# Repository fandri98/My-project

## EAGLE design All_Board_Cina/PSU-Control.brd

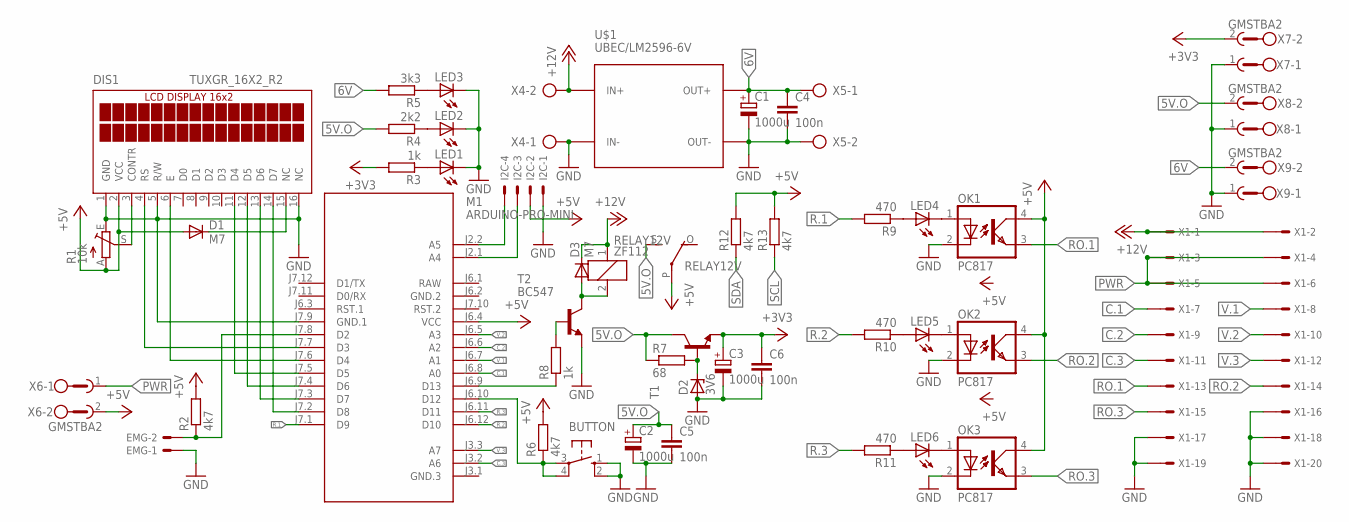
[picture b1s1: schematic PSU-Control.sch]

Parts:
BUTTON: 40-XX; B3F-40XX
C1, C2, C3: 1000u; E5-10,5
C4, C5, C6: 100n; C0805K
D1, D3: M7; DO214AA
D2: 3V6; ZDIO-7.5
DIS1: TUXGR_16X2_R2
EMG: 22-23-2021
I2C: 22-23-2041
LED1, LED2, LED3, LED4, LED5, LED6: LEDCHIPLED_1206; CHIPLED_1206
M1: ARDUINO-PRO-MINI; ARDUINO-PRO-MINI#NP
OK1, OK2, OK3: PC817; DIL04
R1: 10k; RJ9W
R2, R6, R12, R13: 4k7; R0805
R3, R8: 1k; R0805
R4: 2k2; R0805
R5: 3k3; R0805
R7: 68; R0805
R9, R10, R11: 470; R0805
RELAY12V: ZF112
T1: -NPN-TO220V; TO220V
T2: BC547; TO92
U$1: UBEC/LM2596-6V; DC-DC-STEP-DOWN-LM2596
X1: 057-020-1
X4, X5: AK300/2
X6, X7, X8, X9: GMSTBA2

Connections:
5V.O: C2.+, C5.1, R4.2, R7.1, RELAY12V.S, T1.2 (C), X8.2
6V: C1.+, C4.1, R5.2, U$1.OUT+, X5.1, X9.2
+3V3: C3.+, C6.1, R3.2, T1.3 (E), X7.2
+5V: D1.A, DIS1.2 (VCC), I2C.2, M1.J6.4 (VCC), OK1.4 (COL), OK2.4 (COL), OK3.4 (COL), R1.A, R2.2, R6.2, R12.2, R13.2, RELAY12V.P, X6.2
+12V: D3.C, RELAY12V.1, U$1.IN+, X1.1, X1.2, X4.2
C.1: M1.J6.8 (A0), X1.7
C.2: M1.J6.6 (A2), X1.9
C.3: M1.J3.2 (A6), X1.11
GND: BUTTON.1 (S), BUTTON.2 (S1), C1.-, C2.-, C3.-, C4.2, C5.2, C6.2, D2.A, DIS1.1 (GND), DIS1.5 (R/W), DIS1.16 (NC), EMG.1, I2C.1, LED1.C, LED2.C, LED3.C, M1.J7.9 (GND.1), OK1.2 (C), OK2.2 (C), OK3.2 (C), R1.E, T2.1 (E), U$1.IN-, U$1.OUT-, X1.16, X1.17, X1.18, X1.19, X1.20, X4.1, X5.2, X7.1, X8.1, X9.1
GND.2: M1.J6.2 (GND.2)
unnamed: EMG.2, M1.J7.8 (D2), R2.1
unnamed: D1.C, DIS1.15 (NC)
unnamed: DIS1.4 (RS), M1.J7.7 (D3)
unnamed: DIS1.3 (CONTR), R1.S
unnamed: DIS1.6 (E), M1.J7.6 (D4)
unnamed: DIS1.11 (D4), M1.J7.5 (D5)
unnamed: LED4.C, OK1.1 (A)
unnamed: LED5.A, R10.1
unnamed: DIS1.12 (D5), M1.J7.4 (D6)
unnamed: DIS1.13 (D6), M1.J7.3 (D7)
unnamed: DIS1.14 (D7), M1.J7.2 (D8)
unnamed: BUTTON.3, BUTTON.4 (P1), M1.J6.10 (D12), R6.1
unnamed: LED1.A, R3.1
unnamed: LED2.A, R4.1
unnamed: LED3.A, R5.1
unnamed: D2.C, R7.2, T1.1 (B)
unnamed: LED5.C, OK2.1 (A)
unnamed: D3.A, RELAY12V.2, T2.3 (C)
unnamed: M1.J6.9 (D13), R8.1
unnamed: R8.2, T2.2 (B)
unnamed: LED6.A, R11.1
unnamed: LED4.A, R9.1
unnamed: LED6.C, OK3.1 (A)
PWR: X1.3, X1.4, X1.5, X1.6, X6.1
R.1: M1.J7.1 (D9), R9.2
R.2: M1.J6.12 (D10), R10.2
R.3: M1.J6.11 (D11), R11.2
RAW: M1.J6.1 (RAW)
RO.1: OK1.3 (EMIT), X1.13
RO.2: OK2.3 (EMIT), X1.14
RO.3: OK3.3 (EMIT), X1.15
SCL: I2C.4, M1.J2.2 (A5), R13.1
SDA: I2C.3, M1.J2.1 (A4), R12.1
V.1: M1.J6.7 (A1), X1.8
V.2: M1.J6.5 (A3), X1.10
V.3: M1.J3.3 (A7), X1.12

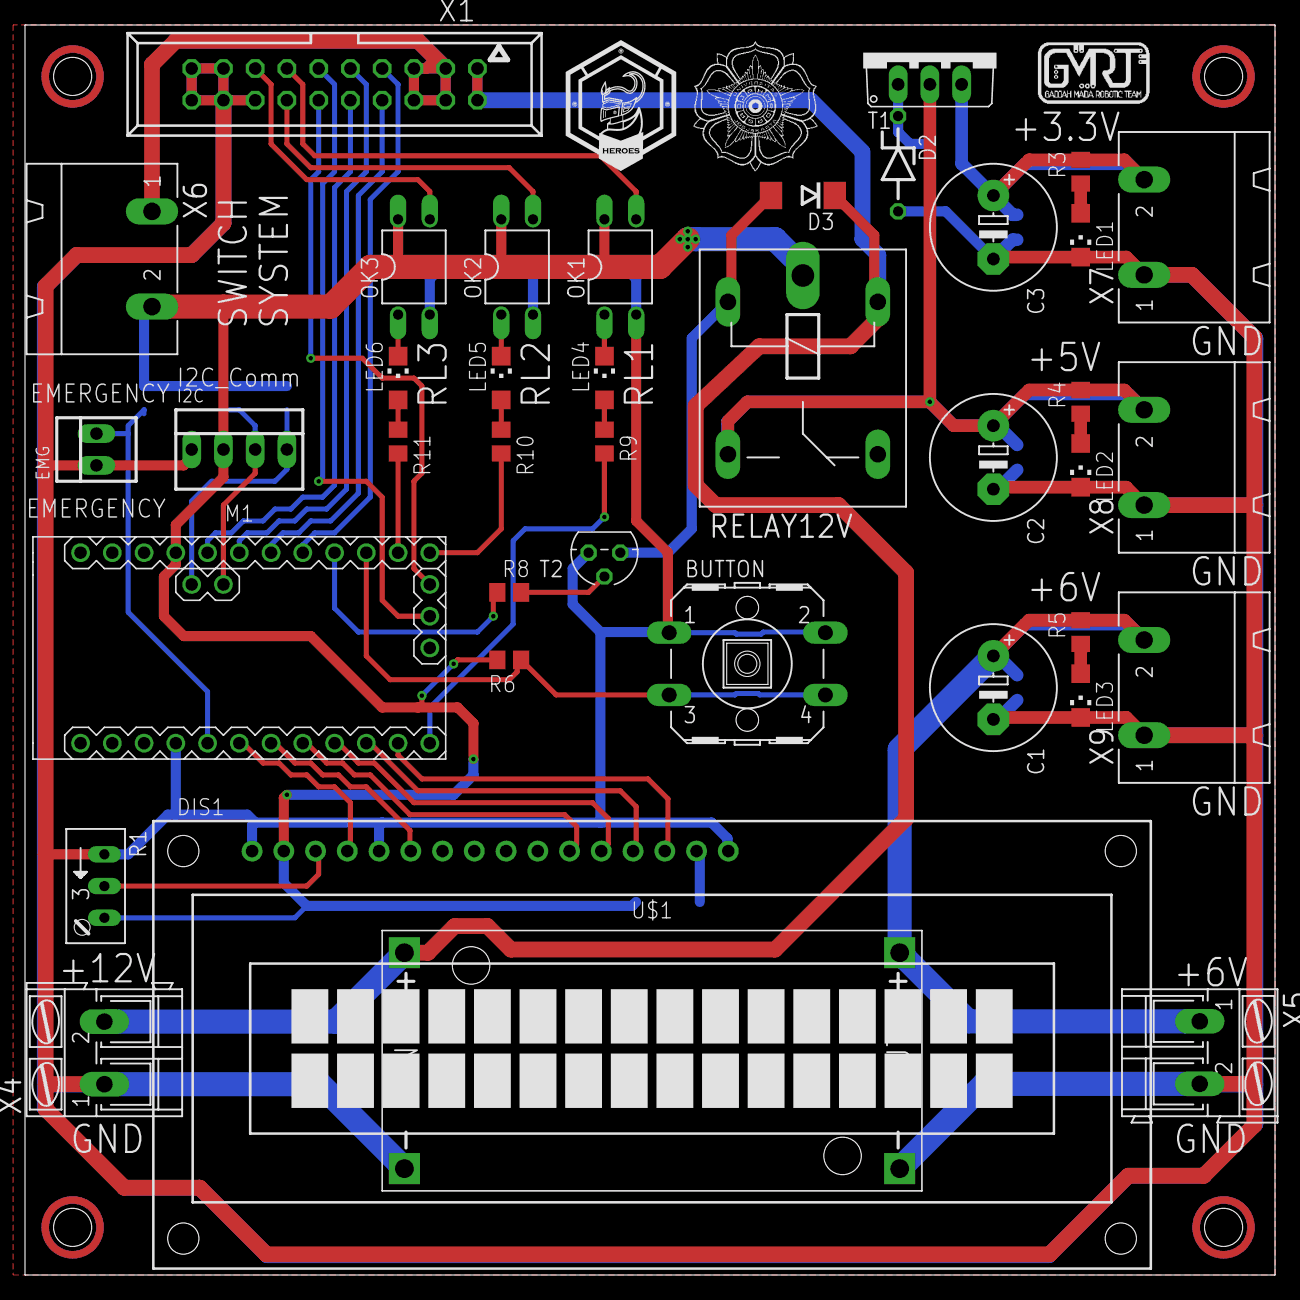
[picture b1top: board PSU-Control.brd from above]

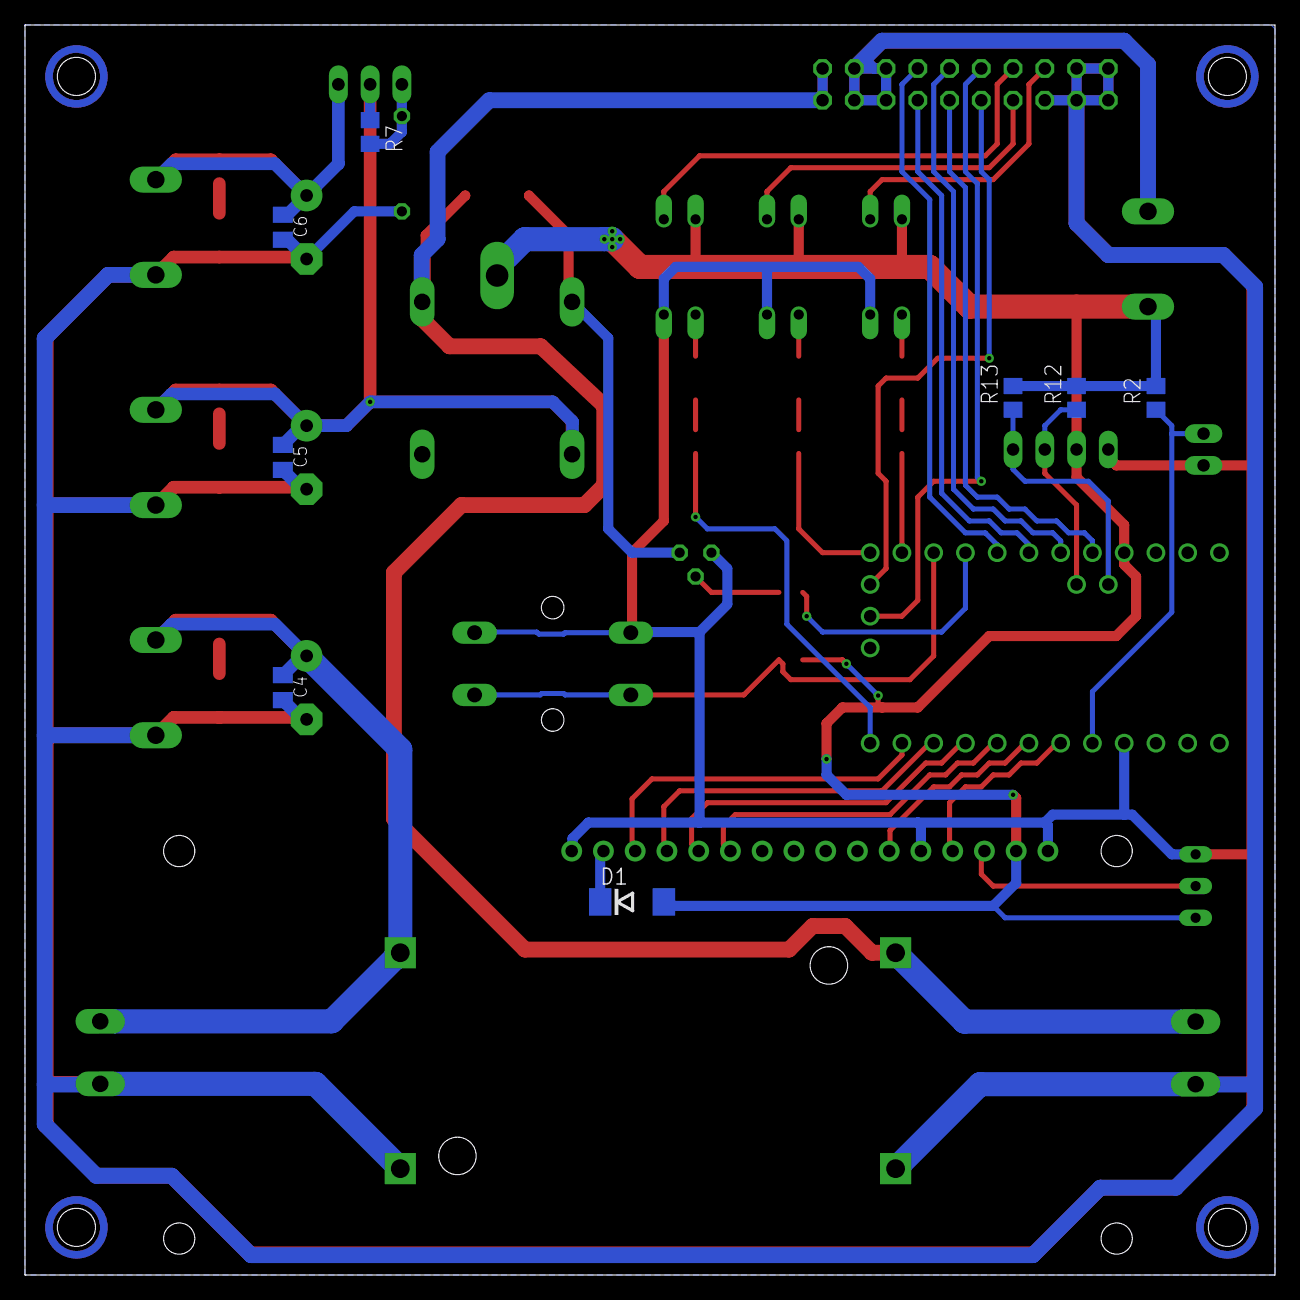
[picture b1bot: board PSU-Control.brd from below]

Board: 2 copper layers, 100.0 x 100.0 mm, 51 parts (8 on the bottom side), 44 nets.

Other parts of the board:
U$2, U$3, U$4, U$5: HOLE-3MM

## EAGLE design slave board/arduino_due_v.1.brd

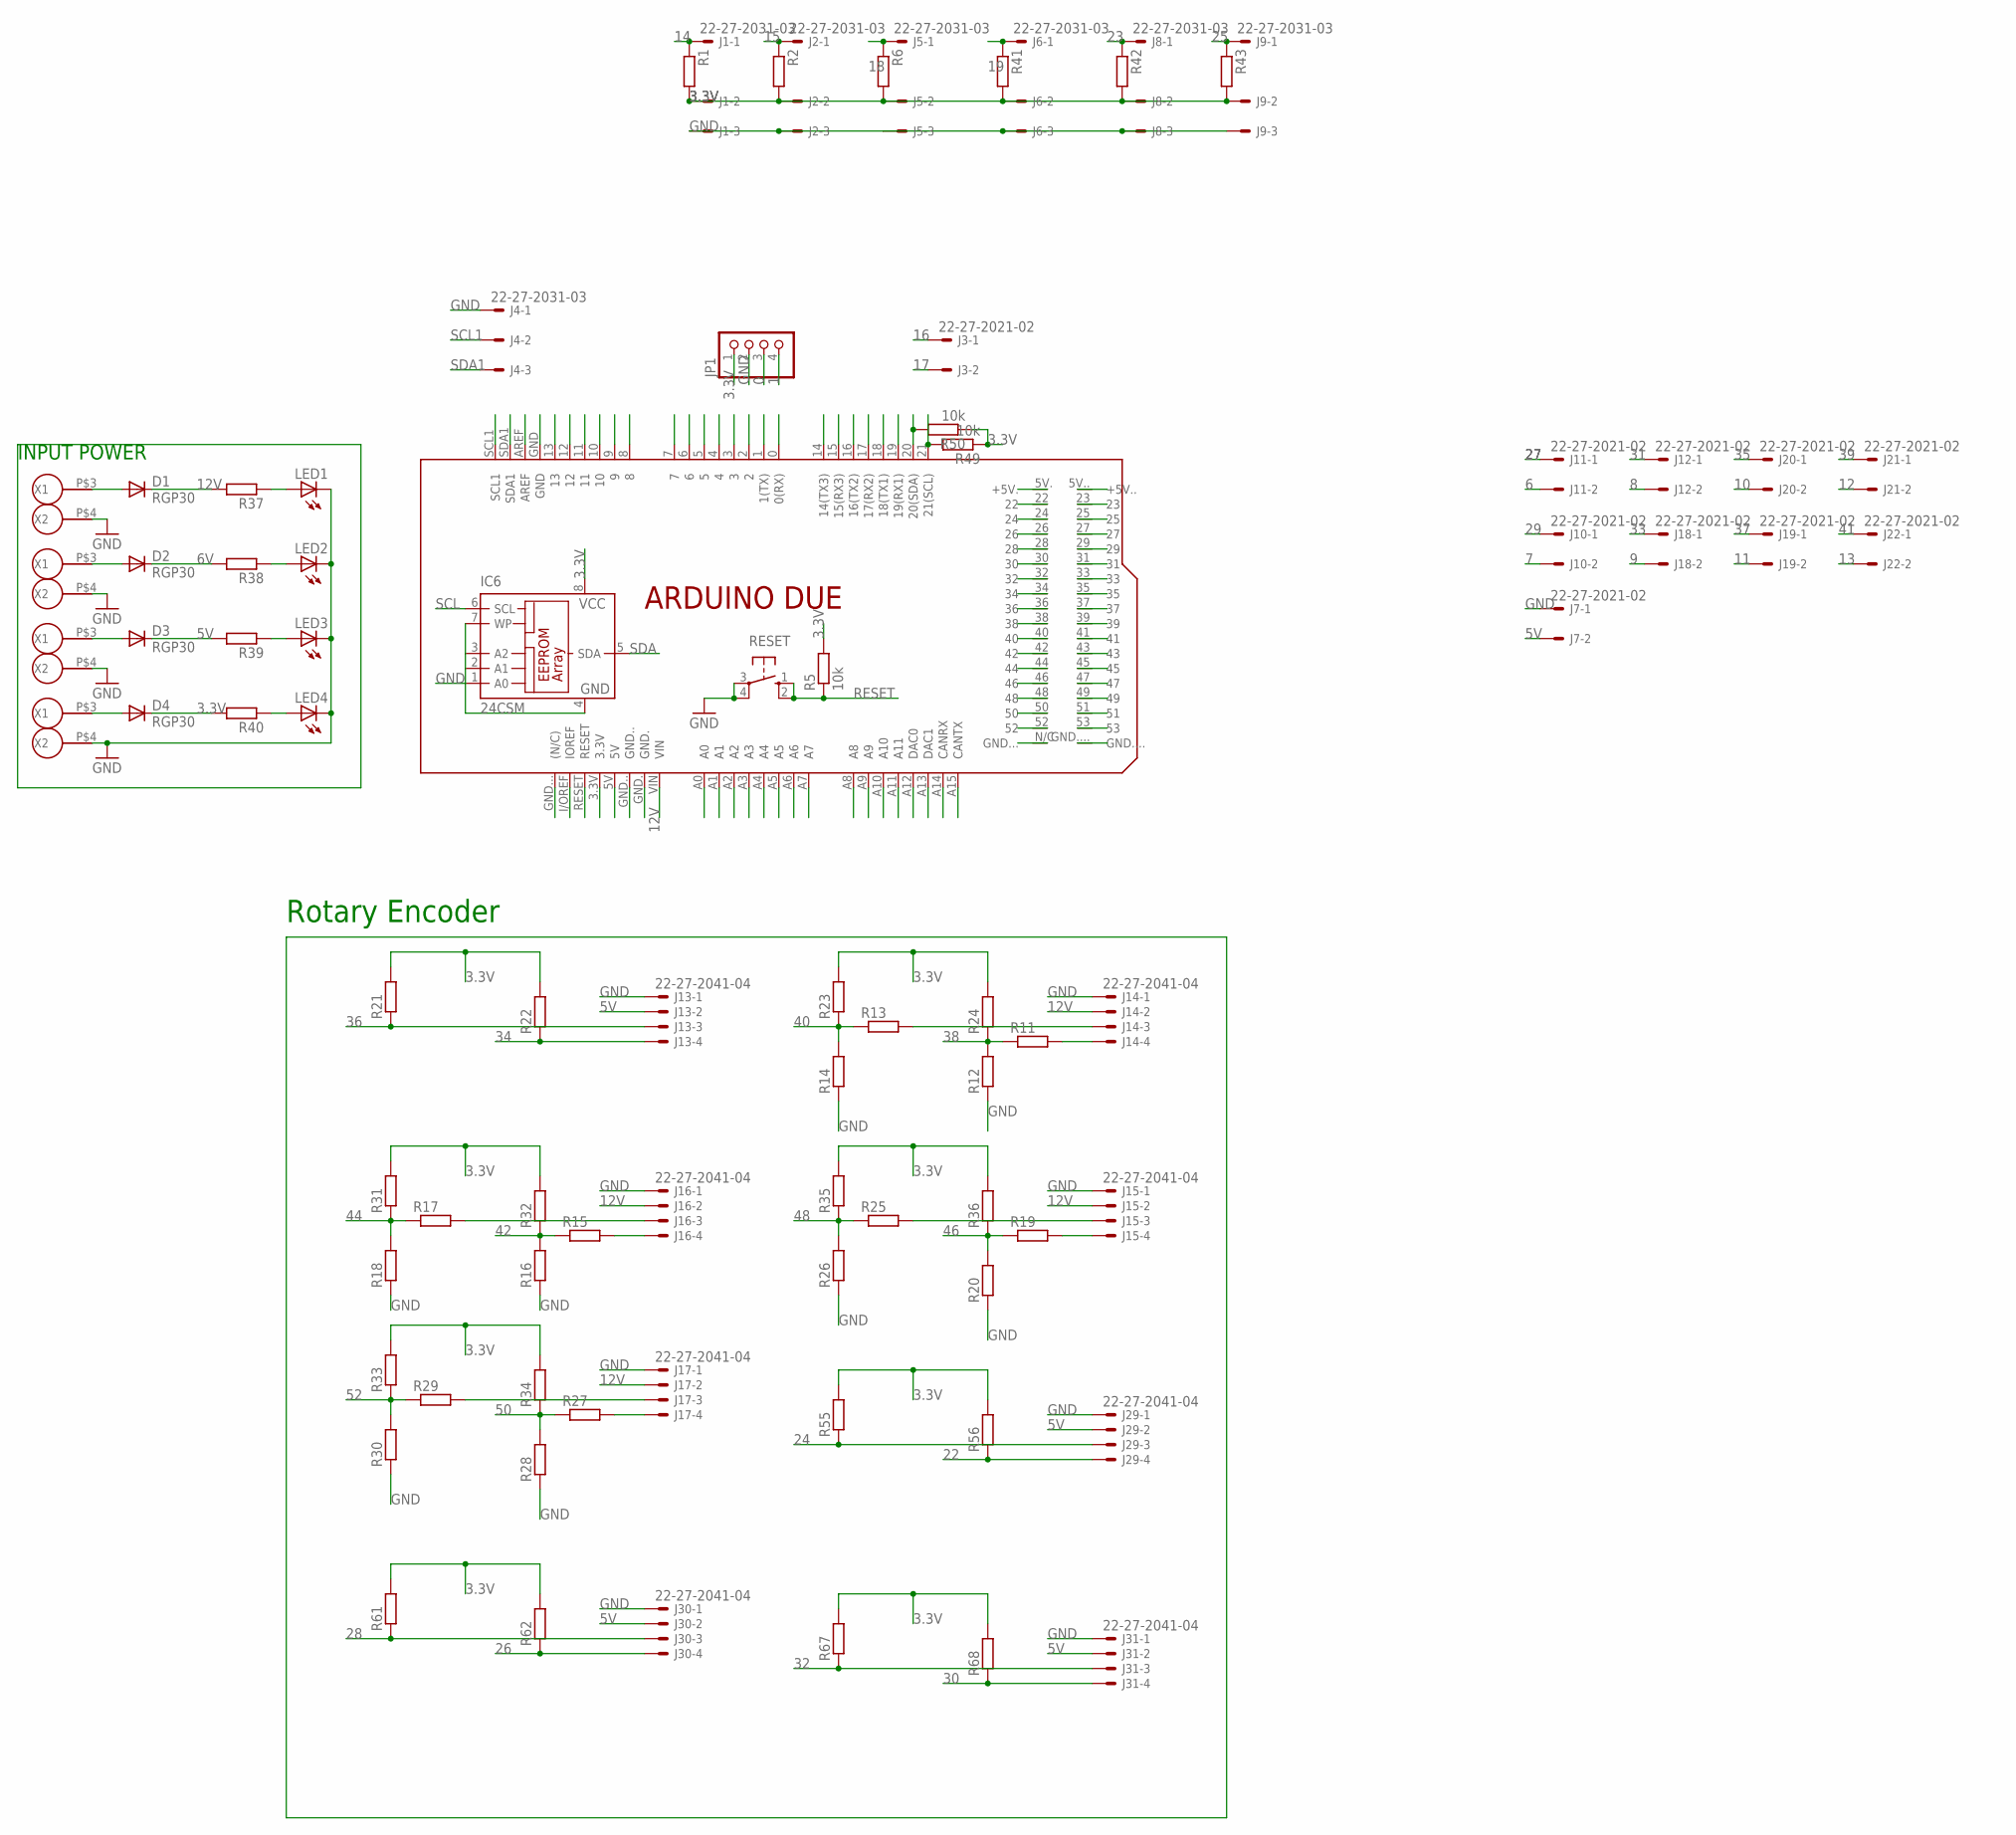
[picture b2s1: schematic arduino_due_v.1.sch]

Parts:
D1, D2, D3, D4: RGP30; DO201-15
IC6: 24CSM; SO-08M; MPN AT24C04BN-SH-B
J1, J2, J4, J5, J6, J8, J9: 22-27-2031-03; 6410-03
J3, J7, J10, J11, J12, J18, J19, J20, J21, J22: 22-27-2021-02; 6410-02
J13, J14, J15, J16, J17, J29, J30, J31: 22-27-2041-04; 6410-04
JP1: PINHD-1X4; 1X04
LED1, LED2, LED3, LED4: LED3MM
PCB1: ARDUINO_DUE
R1, R2, R6, R11, R12, R13, R14, R15, R16, R17, R18, R19, R20, R21, R22, R23, R24, R25, R26, R27, R28, R29, R30, R31, R32, R33, R34, R35, R36, R37, R38, R39, R40, R41, R42, R43, R55, R56, R61, R62, R67, R68: R-EU_M0805; M0805
R5, R49, R50: 10k; M0805
RESET: 40-XX; B3F-40XX
U$1, U$2, U$3, U$8: TB9.5

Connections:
0: JP1.3, PCB1.0 (0(RX))
1: JP1.4, PCB1.1 (1(TX))
2: PCB1.2
3: PCB1.3
3.3V: D4.C, IC6.8 (VCC), J1.2, J2.2, J5.2, J6.2, J8.2, J9.2, JP1.1, R1.2, R2.2, R5.2, R6.2, R21.2, R22.2, R23.2, R24.2, R31.2, R32.2, R33.2, R34.2, R35.2, R36.2, R40.2, R41.2, R42.2, R43.2, R49.1, R50.1, R55.2, R56.2, R61.2, R62.2, R67.2, R68.2
4: PCB1.4
5: PCB1.5
5V: D3.C, J7.2, J13.2, J29.2, J30.2, J31.2, R39.2
6: J11.2, PCB1.6
6V: D2.C, R38.2
7: J10.2, PCB1.7
8: J12.2, PCB1.8
9: J18.2, PCB1.9
10: J20.2, PCB1.10
11: J19.2, PCB1.11
12: J21.2, PCB1.12
12V: D1.C, J14.2, J15.2, J16.2, J17.2, PCB1.VIN, R37.2
13: J22.2, PCB1.13
14: J1.1, PCB1.14 (14(TX3)), R1.1
15: J2.1, PCB1.15 (15(RX3)), R2.1
16: J3.1, PCB1.16 (16(TX2))
17: J3.2, PCB1.17 (17(RX2))
18: J5.1, PCB1.18 (18(TX1)), R6.1
19: J6.1, PCB1.19 (19(RX1)), R41.1
22: J29.4, PCB1.22, R56.1
23: J8.1, PCB1.23, R42.1
24: J29.3, PCB1.24, R55.1
25: J9.1, PCB1.25, R43.1
26: J30.4, PCB1.26, R62.1
27: J11.1, PCB1.27
28: J30.3, PCB1.28, R61.1
29: J10.1, PCB1.29
30: J31.4, PCB1.30, R68.1
31: J12.1, PCB1.31
32: J31.3, PCB1.32, R67.1
33: J18.1, PCB1.33
34: J13.4, PCB1.34, R22.1
35: J20.1, PCB1.35
36: J13.3, PCB1.36, R21.1
37: J19.1, PCB1.37
38: PCB1.38, R11.1, R12.2, R24.1
39: J21.1, PCB1.39
40: PCB1.40, R13.1, R14.2, R23.1
41: J22.1, PCB1.41
42: PCB1.42, R15.1, R16.2, R32.1
43: PCB1.43
44: PCB1.44, R17.1, R18.2, R31.1
45: PCB1.45
46: PCB1.46, R19.1, R20.2, R36.1
47: PCB1.47
48: PCB1.48, R25.1, R26.2, R35.1
49: PCB1.49
50: PCB1.50, R27.1, R28.2, R34.1
51: PCB1.51
52: PCB1.52, R29.1, R30.2, R33.1
53: PCB1.53
A0: PCB1.A0
A1: PCB1.A1
A2: PCB1.A2
A3: PCB1.A3
A4: PCB1.A4
A5: PCB1.A5
A6: PCB1.A6
A7: PCB1.A7
A8: PCB1.A8
A9: PCB1.A9
A10: PCB1.A10
A11: PCB1.A11
A12: PCB1.A12 (DAC0)
A13: PCB1.A13 (DAC1)
A14: PCB1.A14 (CANRX)
A15: PCB1.A15 (CANTX)
AREF: PCB1.AREF
GND: IC6.1 (A0), IC6.2 (A1), IC6.3 (A2), IC6.4 (GND), IC6.7 (WP), J1.3, J2.3, J4.1, J5.3, J6.3, J7.1, J8.3, J9.3, J13.1, J14.1, J15.1, J16.1, J17.1, J29.1, J30.1, J31.1, JP1.2, LED1.K (C), LED2.K (C), LED3.K (C), LED4.K (C), PCB1.GND, R12.1, R14.1, R16.1, R18.1, R20.1, R26.1, R28.1, R30.1, RESET.3, RESET.4 (P1), U$1.P$4 (X2), U$2.P$4 (X2), U$3.P$4 (X2), U$8.P$4 (X2)
unnamed: LED1.A, R37.1
unnamed: LED2.A, R38.1
unnamed: J14.4, R11.2
unnamed: J14.3, R13.2
unnamed: D1.A, U$8.P$3 (X1)
unnamed: D2.A, U$1.P$3 (X1)
unnamed: J16.4, R15.2
unnamed: J16.3, R17.2
unnamed: J15.4, R19.2
unnamed: J15.3, R25.2
unnamed: J17.4, R27.2
unnamed: J17.3, R29.2
unnamed: D3.A, U$2.P$3 (X1)
unnamed: D4.A, U$3.P$3 (X1)
unnamed: LED3.A, R39.1
unnamed: LED4.A, R40.1
RESET: PCB1.RESET, R5.1, RESET.1 (S), RESET.2 (S1)
SCL: IC6.6 (SCL), PCB1.21 (21(SCL)), R49.2
SCL1: J4.2, PCB1.SCL1
SDA: IC6.5 (SDA), PCB1.20 (20(SDA)), R50.2
SDA1: J4.3, PCB1.SDA1

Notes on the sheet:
INPUT POWER
Rotary Encoder

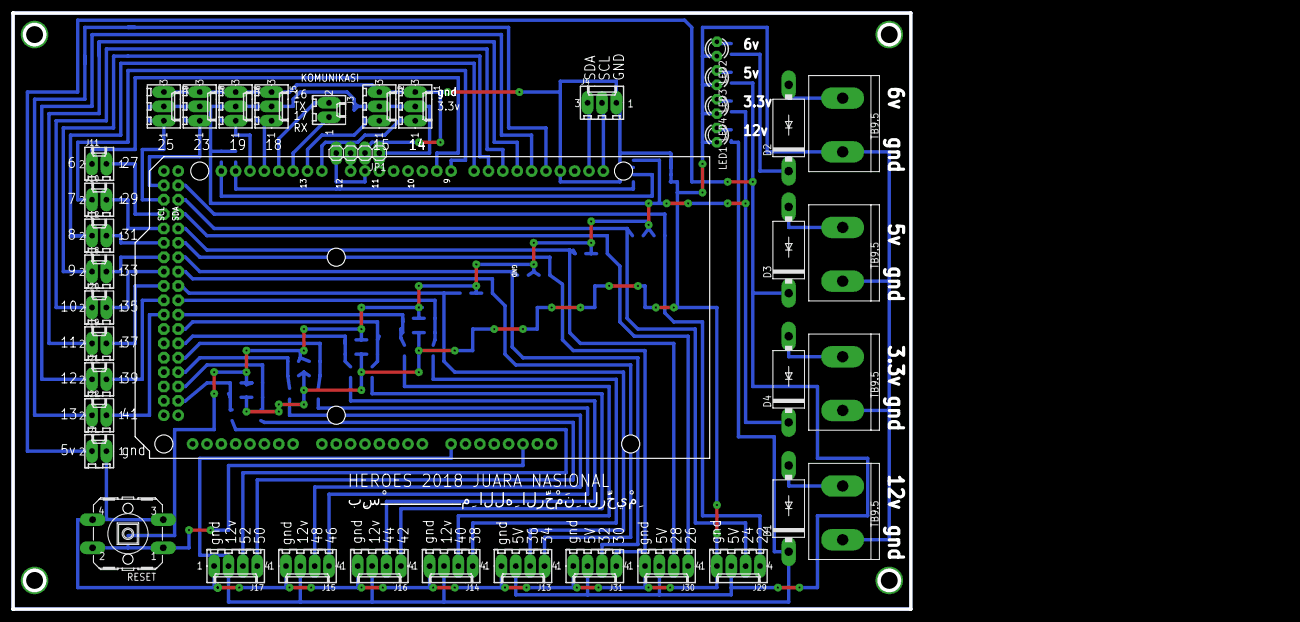
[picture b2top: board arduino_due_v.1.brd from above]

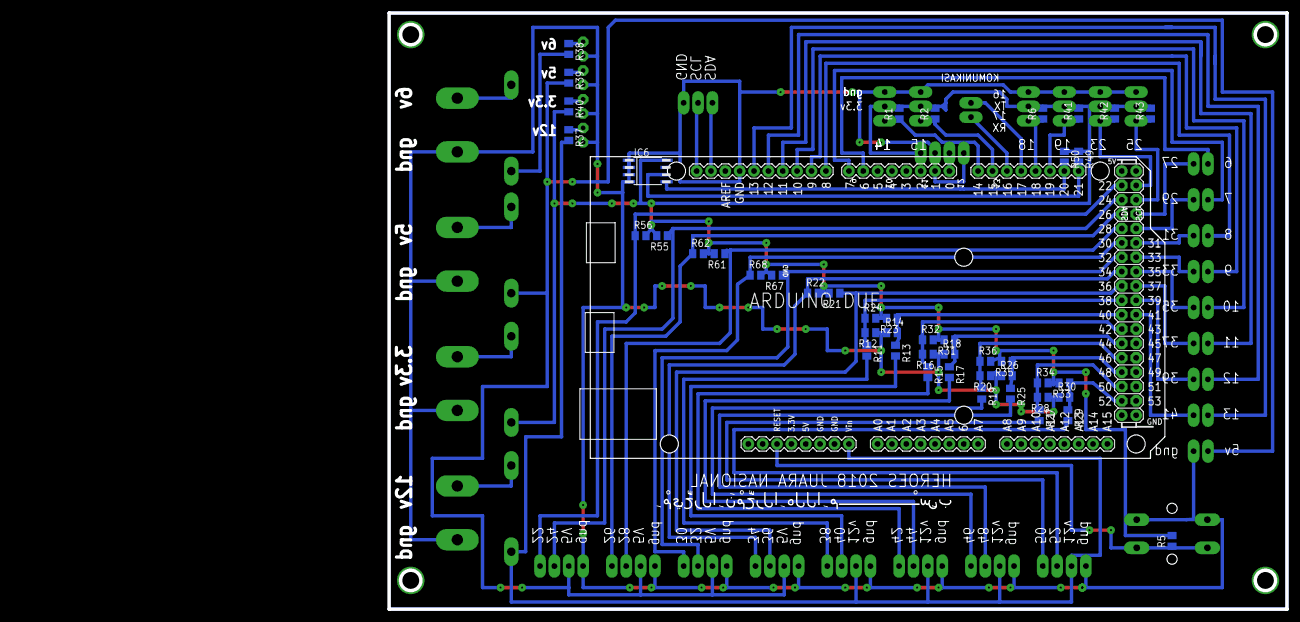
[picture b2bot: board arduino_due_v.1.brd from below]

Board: 2 copper layers, 158.8 x 105.4 mm, 86 parts (47 on the bottom side), 68 nets.

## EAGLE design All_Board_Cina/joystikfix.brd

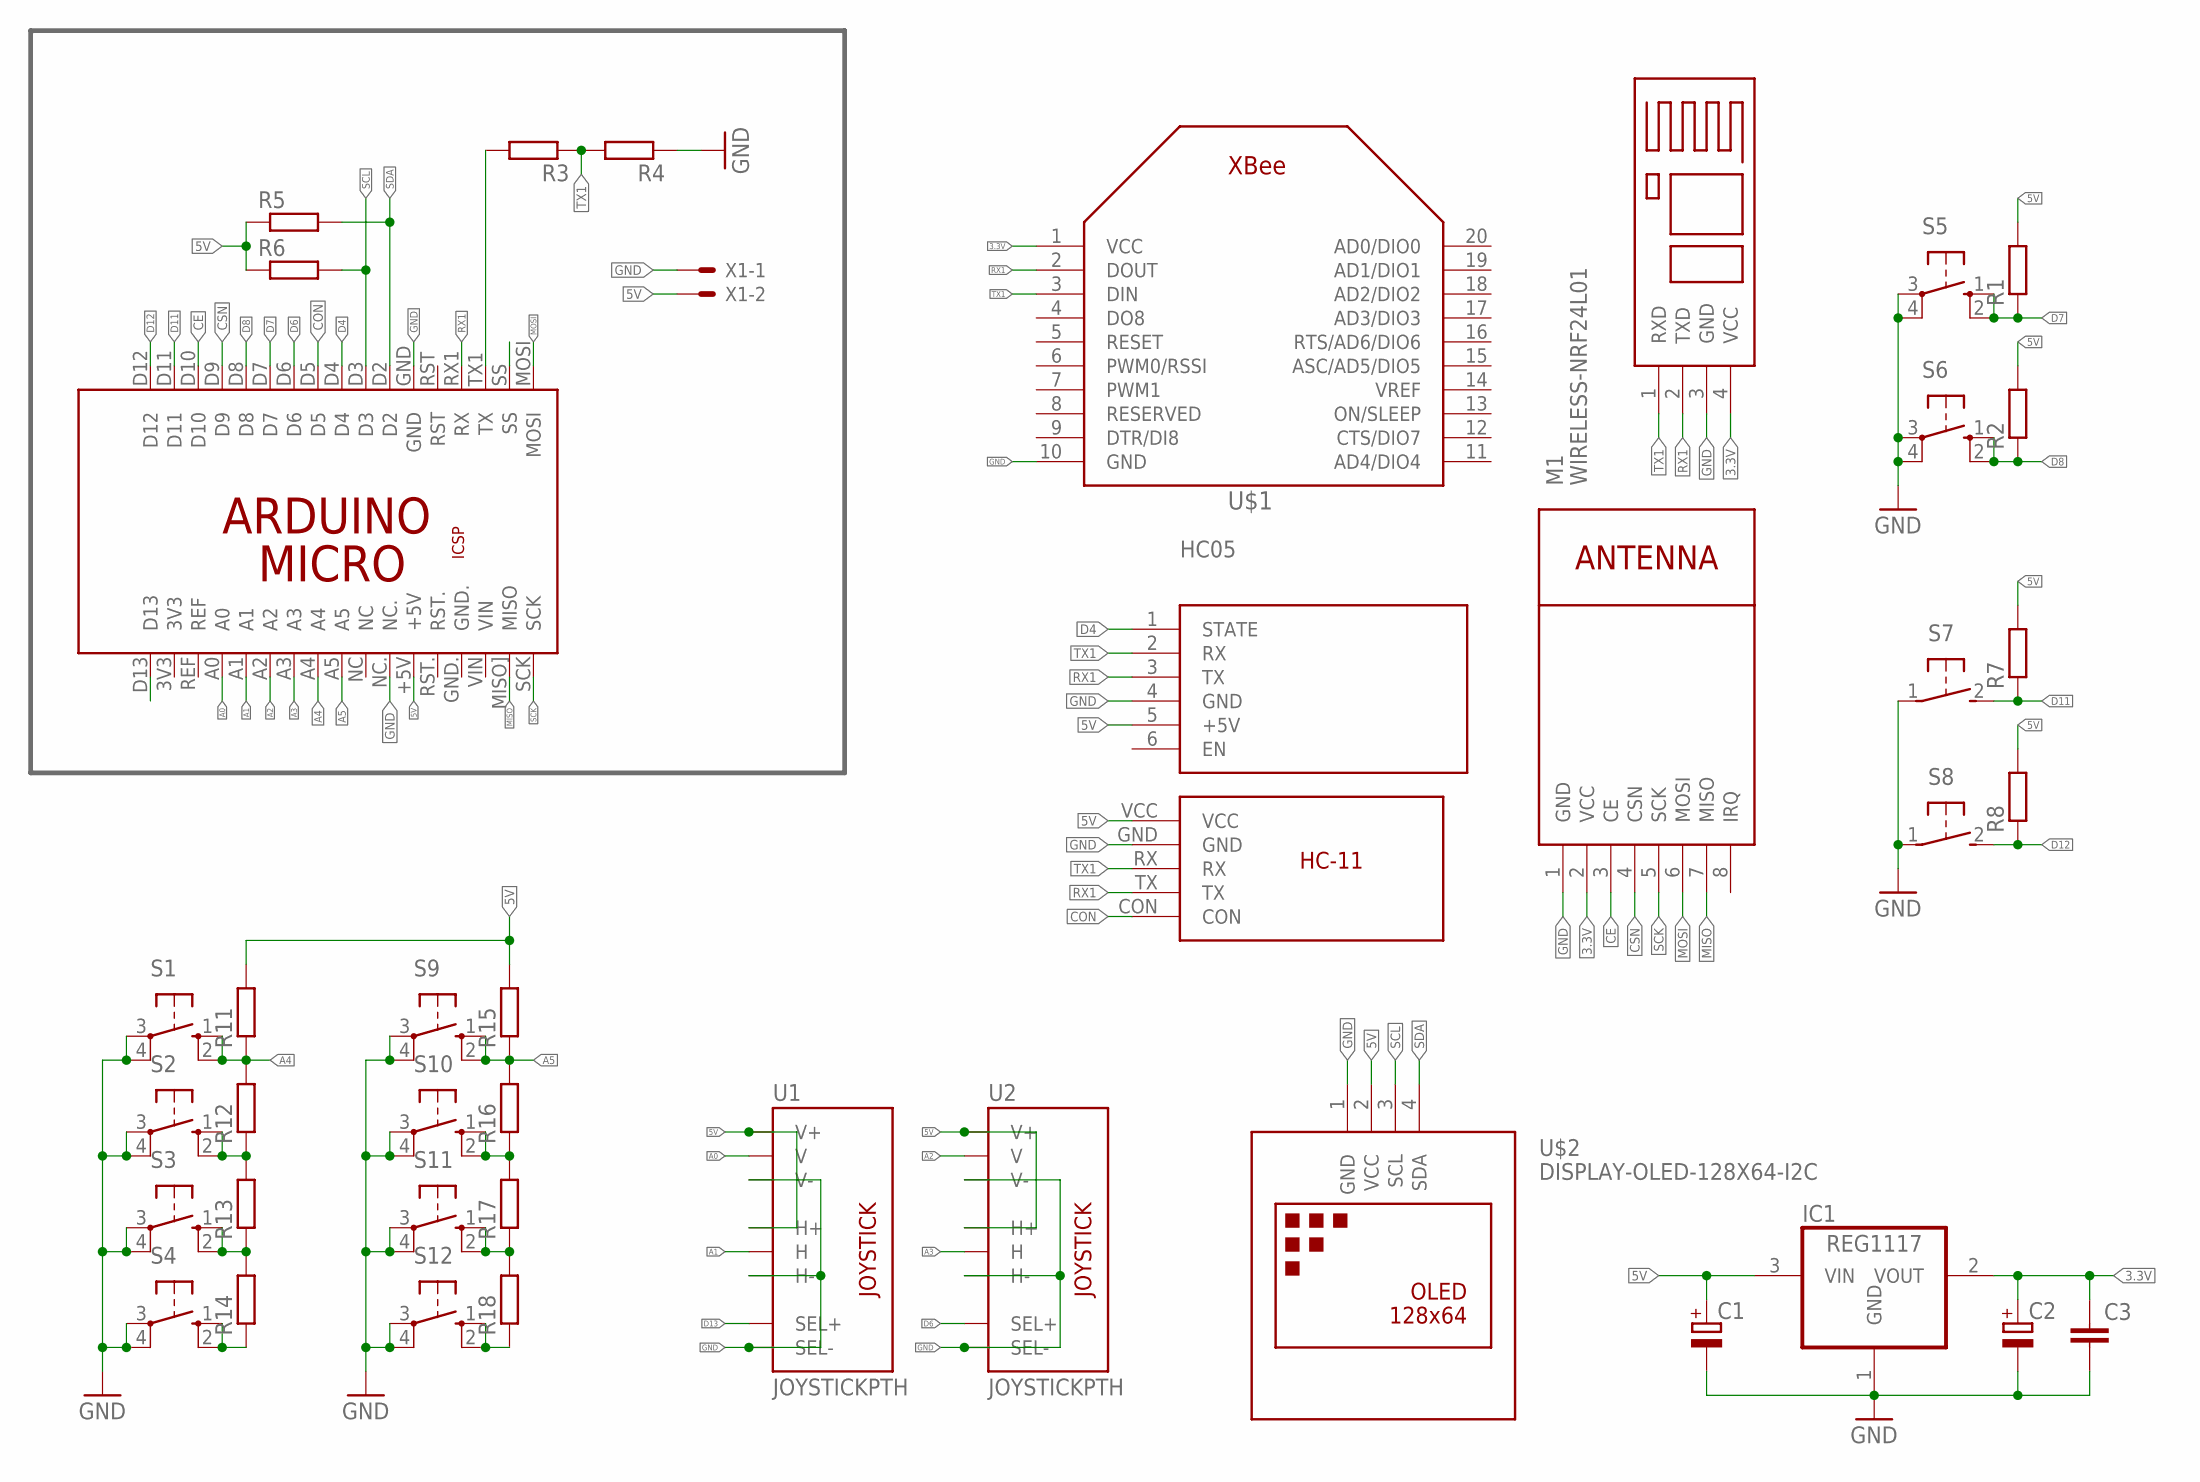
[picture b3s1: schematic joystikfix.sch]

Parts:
C1, C2: CPOL-EUA/3216-18W; A/3216-18W
C3: C-EUC0805K; C0805K
HC05: WIRELESS-BLUETOOTH-HC-05
HM10: BLUETOOTH
IC1: REG1117; SOT223
M1: WIRELESS-NRF24L01
PCB1: ARDUINO_MICRO
R1, R2, R3, R4, R5, R6, R7, R8, R11, R12, R13, R14, R15, R16, R17, R18: R-EU_M0805; M0805
S1, S2, S3, S4, S9, S10, S11, S12: 40-XX; B3F-40XX
S5, S6: 10-XX; B3F-10XX
S7, S8: 31-XX; B3F-31XX
U1, U2: JOYSTICKPTH; JOYSTICK
U$1: XBEE
U$2: DISPLAY-OLED-128X64-I2C
U$3: HC-11
X1: 22-23-2021

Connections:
3.3V: C2.+, C3.1, HM10.4 (VCC), IC1.2 (VOUT), M1.2 (VCC), U$1.1 (VCC)
5V: C1.+, HC05.5 (+5V), IC1.3 (VIN), PCB1.+5V, R1.2, R2.2, R5.1, R6.1, R7.2, R8.2, R11.2, R15.2, U1.H1 (H+), U1.V1 (V+), U2.H1 (H+), U2.V1 (V+), U$2.2 (VCC), U$3.VCC, X1.2
A0: PCB1.A0, U1.V2 (V)
A1: PCB1.A1, U1.H2 (H)
A2: PCB1.A2, U2.V2 (V)
A3: PCB1.A3, U2.H2 (H)
A4: PCB1.A4, R11.1, R12.2, S1.1 (S), S1.2 (S1)
A5: PCB1.A5, R15.1, R16.2, S9.1 (S), S9.2 (S1)
CE: M1.3 (CE), PCB1.D10
CON: PCB1.D5, U$3.CON
CSN: M1.4 (CSN), PCB1.D9
D4: HC05.1 (STATE), PCB1.D4
D6: PCB1.D6, U2.B1A (SEL+)
D7: PCB1.D7, R1.1, S5.1 (S), S5.2 (S1)
D8: PCB1.D8, R2.1, S6.1 (S), S6.2 (S1)
D11: PCB1.D11, R7.1, S7.2 (S)
D12: PCB1.D12, R8.1, S8.2 (S)
D13: PCB1.D13, U1.B1A (SEL+)
GND: C1.-, C2.-, C3.2, HC05.4 (GND), HM10.3 (GND), IC1.1 (GND), M1.1 (GND), PCB1.GND, PCB1.NC., R4.1, S1.3, S1.4 (P1), S2.3, S2.4 (P1), S3.3, S3.4 (P1), S4.3, S4.4 (P1), S5.3, S5.4 (P1), S6.3, S6.4 (P1), S7.1, S8.1, S9.3, S9.4 (P1), S10.3, S10.4 (P1), S11.3, S11.4 (P1), S12.3, S12.4 (P1), U1.B2A (SEL-), U1.H3 (H-), U1.V3 (V-), U2.B2A (SEL-), U2.H3 (H-), U2.V3 (V-), U$1.10 (GND), U$2.1 (GND), U$3.GND, X1.1
MISO: M1.7 (MISO), PCB1.MISO] (MISO)
MOSI: M1.6 (MOSI), PCB1.MOSI
unnamed: PCB1.TX1 (TX), R3.2
unnamed: R12.1, R13.2, S2.1 (S), S2.2 (S1)
unnamed: R13.1, R14.2, S3.1 (S), S3.2 (S1)
unnamed: R14.1, S4.1 (S), S4.2 (S1)
unnamed: R16.1, R17.2, S10.1 (S), S10.2 (S1)
unnamed: R17.1, R18.2, S11.1 (S), S11.2 (S1)
unnamed: R18.1, S12.1 (S), S12.2 (S1)
RX1: HC05.3 (TX), HM10.2 (TXD), PCB1.RX1 (RX), U$1.2 (DOUT), U$3.TX
SCK: M1.5 (SCK), PCB1.SCK
SCL: PCB1.D3, R6.2, U$2.3 (SCL)
SDA: PCB1.D2, R5.2, U$2.4 (SDA)
TX1: HC05.2 (RX), HM10.1 (RXD), R3.1, R4.2, U$1.3 (DIN), U$3.RX

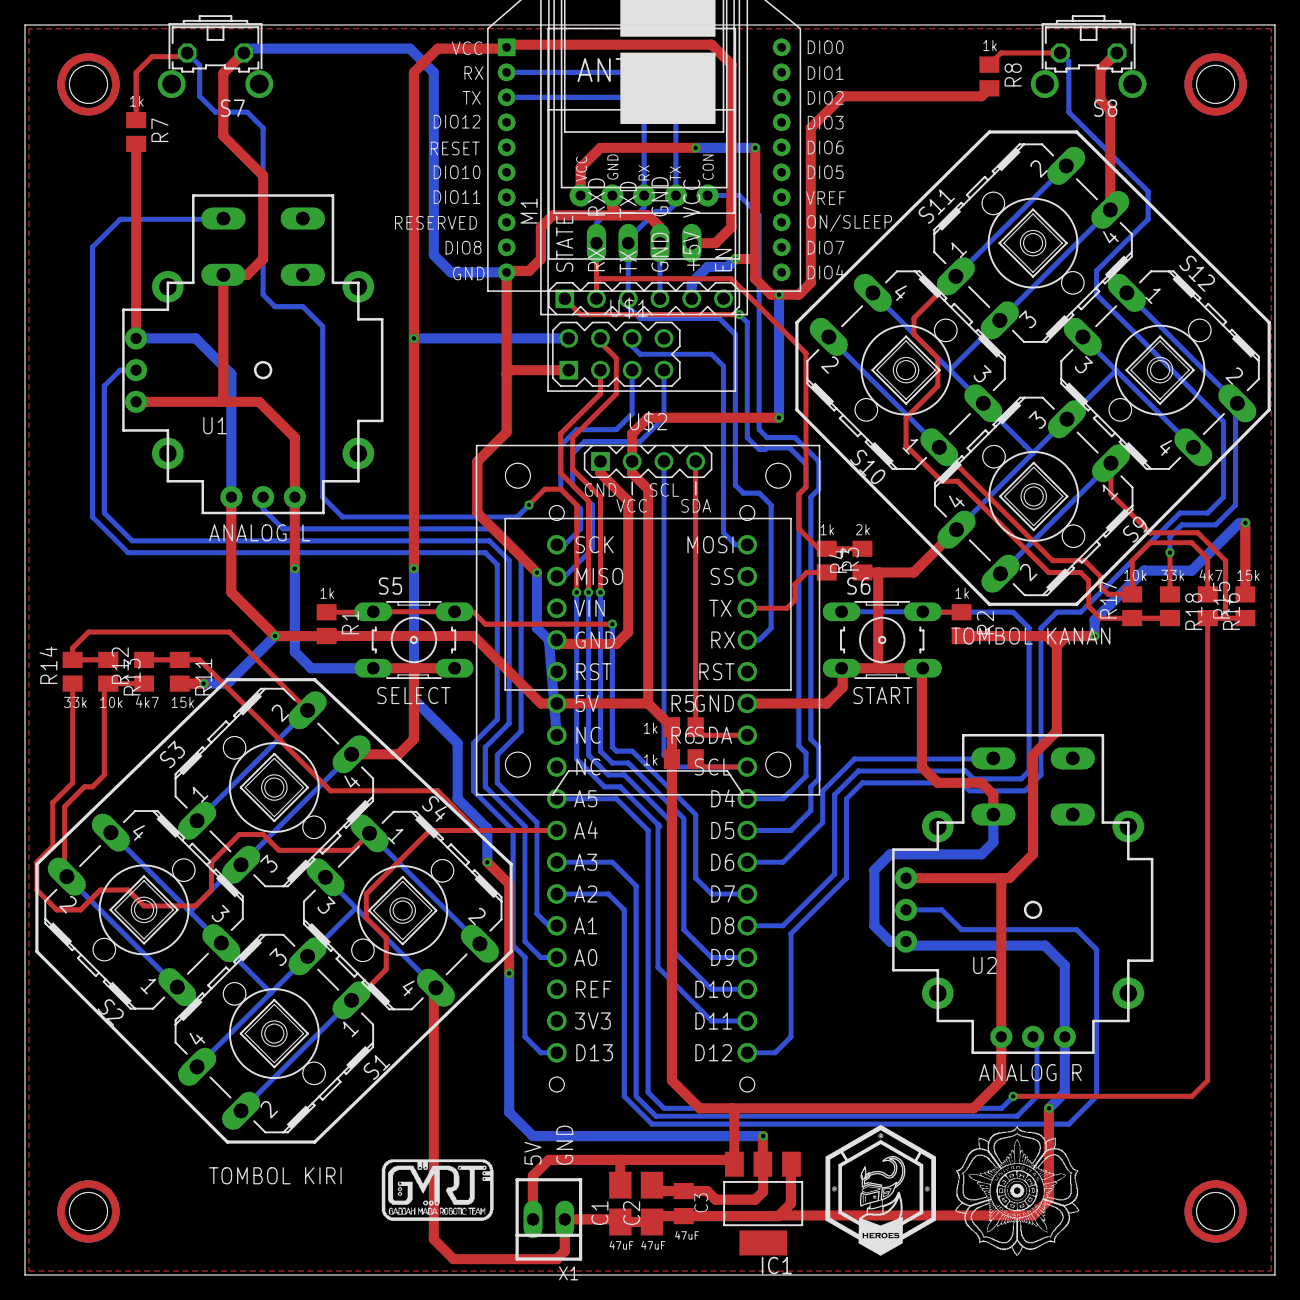
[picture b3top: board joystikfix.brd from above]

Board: 2 copper layers, 100.0 x 100.0 mm, 46 parts (1 on the bottom side), 33 nets.

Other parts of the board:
U$4, U$5, U$6, U$7: HOLE-3MM

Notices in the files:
parts and their libraries:
diy-modules: Released under the Creative Commons Attribution 4.0 International License: http://creativecommons.org/licenses/by/4.0
